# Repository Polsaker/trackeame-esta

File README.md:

# Trackeame esta
GPS/GSM tracker

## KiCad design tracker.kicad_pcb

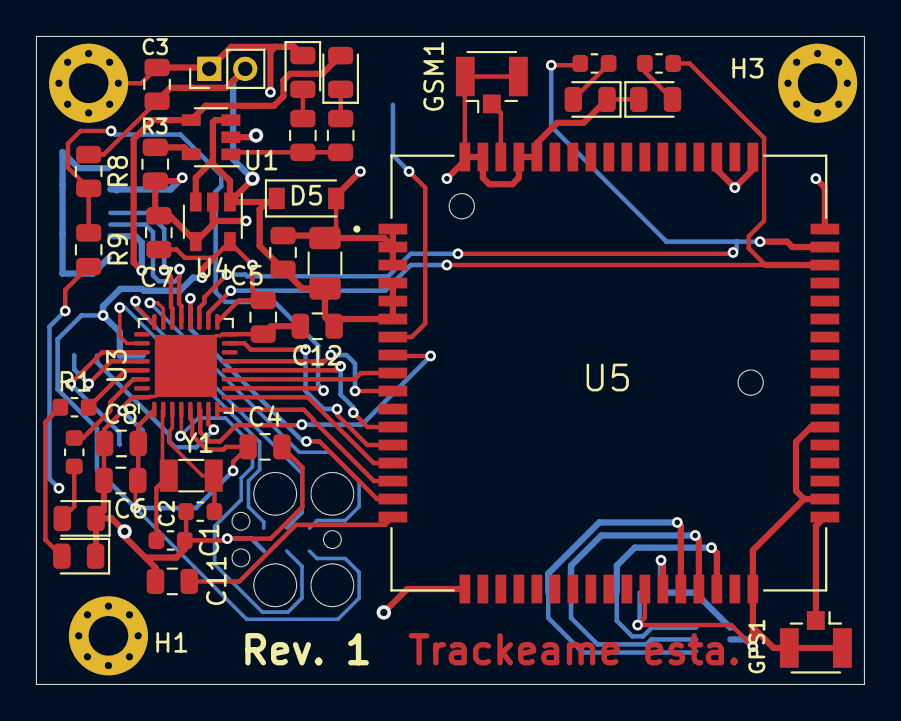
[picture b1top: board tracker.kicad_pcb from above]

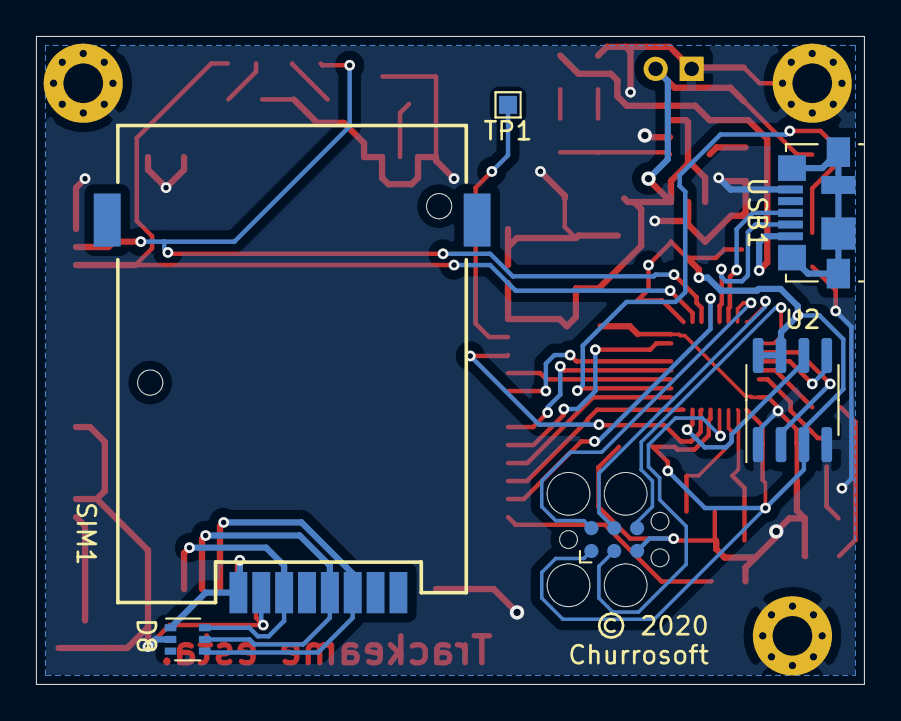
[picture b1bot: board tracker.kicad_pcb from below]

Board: 2 copper layers, 46.0 x 36.0 mm, 45 parts (6 on the bottom side), 44 nets.

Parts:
C1, C2: 3.3pF; C_0603_1608Metric
C3, C7: 1uF; C_0805_2012Metric
C4: 10nF; C_0805_2012Metric
C5, C6: 100nF; C_0805_2012Metric
C8, C11: 4.7uF; C_0805_2012Metric
C9: 100uF; C_1206_3216Metric
C10: 33pF; C_0805_2012Metric
C12: 10pF; C_0805_2012Metric
D1: Red; LED_0805_2012Metric
D2, D3: Orange; LED_0805_2012Metric
D4, D6: Green; LED_0805_2012Metric
D5: MMSZ5231BT1G; D_SOD-123
D7: Blue; LED_0805_2012Metric
D8: SMF05; SOT-363_SC-70-6
GPS1: Conn_Coaxial; U.FL_Hirose_U.FL-R-SMT-1_Vertical
GSM1: Conn_Coaxial; U.FL_Hirose_U.FL-R-SMT-1_Vertical
H1, H2, H3: MountingHole; MountingHole_2.2mm_M2_Pad_Via
J2: Tag connect; Tag-Connect_TC2030-IDC-FP_2x03_P1.27mm_Vertical
J6: BATT; PinHeader_1x02_P2.00mm_Vertical
R1, R2, R6, R7: 4.7k; R_0603_1608Metric
R3: 2k; R_0805_2012Metric
R4: 470R; R_0805_2012Metric
R5: 1k; R_0805_2012Metric
R8, R9: 100k; R_0805_2012Metric
SIM1: MOLEX47553-2001; MOLEX_47553-2001
TP1: VDD_EXT; TestPoint_Pad_1.0x1.0mm
U1: MCP73831-2-OT; SOT-23-5
U2: W25X40CL; SOIC-8_3.9x4.9mm_P1.27mm
U3: STM32L432KBUx; QFN-32-1EP_5x5mm_P0.5mm_EP3.45x3.45mm
U4: TPS78233DDC; SOT-23-5
U5: SIM808; XCVR_SIM808
USB1: USB_B_Micro; USB_Micro-B_Molex_47346-0001
Y1: 32.768KHz; Crystal_SMD_3215-2Pin_3.2x1.5mm

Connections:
+3V3: C4.1, C5.1, C6.1, C7.1, C8.1, J2.1, U2.3, U2.7, U2.8, U3.1, U3.5, U3.17, U4.5
+5V: D3.2, U1.4, USB1.1
/ADC1_IN9: R8.2, R9.1, U3.10
/LED1: R2.2, U3.30
/LED2: R1.2, U3.29
/NRST: J2.3, U3.4
/SPI1_MISO: U2.2, U3.27
/SPI1_MOSI: U2.5, U3.28
/SPI1_SCK: U2.6, U3.7
/SYS_SWCLK: J2.4, U3.24
/SYS_SWDIO: J2.2, U3.23
/SYS_SWO: J2.6, U3.26
/USB_D+: U3.22, USB1.3
/USB_D-: U3.21, USB1.2
GND: C1.2, C2.2, C3.2, C4.2, C5.2, C6.2, C7.2, C8.2, C9.2, C10.1, C11.2, C12.2, D1.1, D2.1, D4.1, D5.2, D6.1, D7.1, D8.2, GPS1.2, GSM1.2, H1.1, H2.1, H3.1, J2.5, J6.1, R3.1, R9.2, SIM1.C5, U1.2, U2.1, U2.4, U3.16, U3.32, U3.33, U4.2, U4.4, U5.1, U5.2, U5.3, U5.18, U5.28, U5.34, U5.36, U5.40, U5.51, U5.52, U5.54, U5.64, U5.65, U5.67, U5.68, USB1.5
NETLIGHT: R6.2, U3.19, U5.50
unnamed: C1.1, U3.2, Y1.1
unnamed: C2.1, U3.3, Y1.2
unnamed: C11.1, U5.17
unnamed: D1.2, R1.1
unnamed: D2.2, R2.1
unnamed: D3.1, R4.1
unnamed: D4.2, R5.1
unnamed: D6.2, R6.1
unnamed: D7.2, R7.1
unnamed: GPS1.1, U5.35
unnamed: GSM1.1, U5.66
unnamed: R3.2, U1.5
unnamed: R4.2, R5.2, U1.1
unnamed: TP1.1, U5.7
PWRKEY: U3.6, U5.8
RESET: U3.20, U5.16
SIM_CLK: D8.5, SIM1.C3, U5.31
SIM_DATA: D8.4, SIM1.C7, U5.30
SIM_RST: D8.6, SIM1.C2, U5.32
SIM_VDD: D8.1, SIM1.C1, U5.29
STATUS: R7.2, U3.18, U5.49
UART_CTS: U3.12, U5.12
UART_DTR: U3.11, U5.9
UART_RI: U3.13, U5.10
UART_RTS: U3.15, U5.13
UART_RXD: U3.8, U5.15
UART_TXD: U3.9, U5.14
VDD: C3.1, C9.1, C10.2, C12.1, D5.1, J6.2, R8.1, U1.3, U4.1, U4.3, U5.4, U5.5, U5.6

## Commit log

2020-10-02 Adding README
2020-10-02 Size reduction
2020-10-03 Wiring VDD to ADC

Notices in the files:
tracker.kicad_pcb:
© 2020
